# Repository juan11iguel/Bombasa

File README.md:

# Bombasa
En este proyecto intentamos implementar un arduino, con un driver para un motor DC y, haciendo uso de periféricos como una pantalla de 4 dígitos y 7 segmentos, así como de botones, interruptores, etc. Establecer dos modos de funcionamiento en un sistema cuyo objetivo es el impulso de reactivos químicos para mezcla de componentes (bomba PERISTÁLTICA*):

- El modo manual tiene como entrada la pulsación de dos botones, uno para aumentar y otro para disminuir, el rango de valores va de 0 a 20, y cada valor se corresponde con un valor de voltaje que se le introduce al motor y que hace propulsar un caudal determinado tras la calibración. El valor escogido, así como el voltaje que le corresponde y su caudal se muestran periódicamente en pantalla, así como en una tabla situada en la parte superior de la caja.
- El modo automático tiene dos opciones de funcionamiento, o bien toma la información de una tarjeta de entrada/salida (Labjack), que proporciona valores comprendidos entre 0 y 5V, el valor es leído por el Arduino en uno de sus puertos analógicos y codificado entre 0 y 1023, lo que a su vez ajusta al valor del PWM (0 - 255) y se introduce al driver. Otra opción es hacer uso de la comunicación por el puerto serie, que admite desde valores de la terminal serie incluída en el entorno de desarrollo de arduino, o bien a través de programas como Matlab (pendiente) o un sencillo programa desarrollado en Python (ya hecho y funcionando). 

Posteriormente, se intentará introducir un caudalímetro contador, que se introducirá en uno de los puertos digitales del Arduino, y se desarrollará un algoritmo para acondicionar esa información entrante y convertirla en un valor de caudal que se actualice cada pocos segundos, esta información se usará para cerrar un lazo de control, y haciendo uso de un controlador tipo PI controlar la bomba. También la idea es mandar la información instantánea del caudal como salida para poder realizar el registro de la información tomada.

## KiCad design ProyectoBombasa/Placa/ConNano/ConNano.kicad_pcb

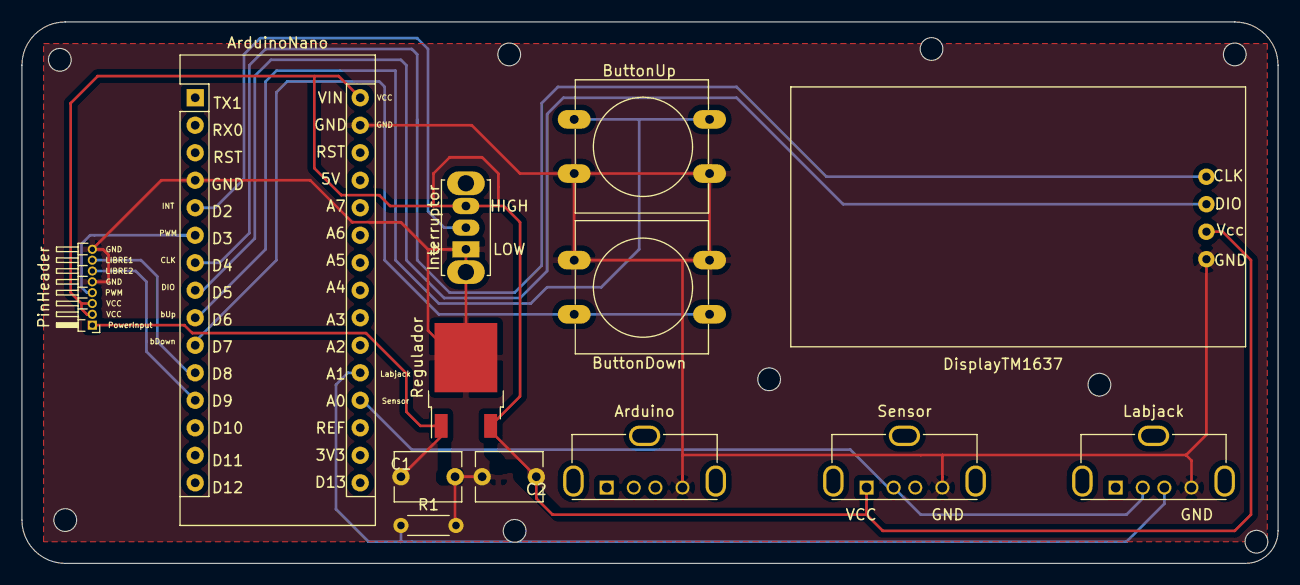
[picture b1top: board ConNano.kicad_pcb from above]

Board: 2 copper layers, 116.0 x 50.0 mm, 13 parts (0 on the bottom side), 13 nets.

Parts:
Arduino: USB_A; USB_A_Molex_105057_Vertical
ArduinoNano: Arduino_Nano_v3.x; Arduino_Nano
ButtonDown: SW_Push; SW_PUSH-12mm
ButtonUp: SW_Push; SW_PUSH-12mm
C1: 0.33uF; C_Disc_D6.0mm_W4.4mm_P5.00mm
C2: 0.1uF; C_Disc_D6.0mm_W4.4mm_P5.00mm
DisplayTM1637: TM1637; TM1637Cool
Interruptor: SW_SPDT; SW_Slide_1P2T_CK_OS102011MS2Q
Labjack: USB_A; USB_A_Molex_105057_Vertical
PinHeader: Conn_01x08; PinHeader_1x08_P1.00mm_Horizontal
R1: 1k; R_Axial_DIN0204_L3.6mm_D1.6mm_P5.08mm_Horizontal
Regulador: L7805; TO-252-2
Sensor: USB_A; USB_A_Molex_105057_Vertical

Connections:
ButtonDown: ArduinoNano.10, ButtonDown.2
ButtonUp: ArduinoNano.9, ButtonUp.1
CLK: ArduinoNano.7, DisplayTM1637.1
DIO: ArduinoNano.8, DisplayTM1637.2
GND: Arduino.4, ArduinoNano.4, ButtonDown.1, ButtonUp.2, C1.2, C2.2, DisplayTM1637.4, Interruptor.1, Labjack.4, PinHeader.5, PinHeader.8, R1.2, Regulador.2, Sensor.4
Interruptor: ArduinoNano.5, Interruptor.2
LabjackSC: ArduinoNano.20, Labjack.3, R1.1
LabjackSensor: ArduinoNano.19, Labjack.2, Sensor.2
PWM: ArduinoNano.6, PinHeader.4
PowerInput: C1.1, PinHeader.1, Regulador.1
Vcc: ArduinoNano.30, C2.1, DisplayTM1637.3, Interruptor.3, PinHeader.2, PinHeader.3, Regulador.3, Sensor.1
porSiAca1: ArduinoNano.11, PinHeader.6
porSiAca2: ArduinoNano.12, PinHeader.7

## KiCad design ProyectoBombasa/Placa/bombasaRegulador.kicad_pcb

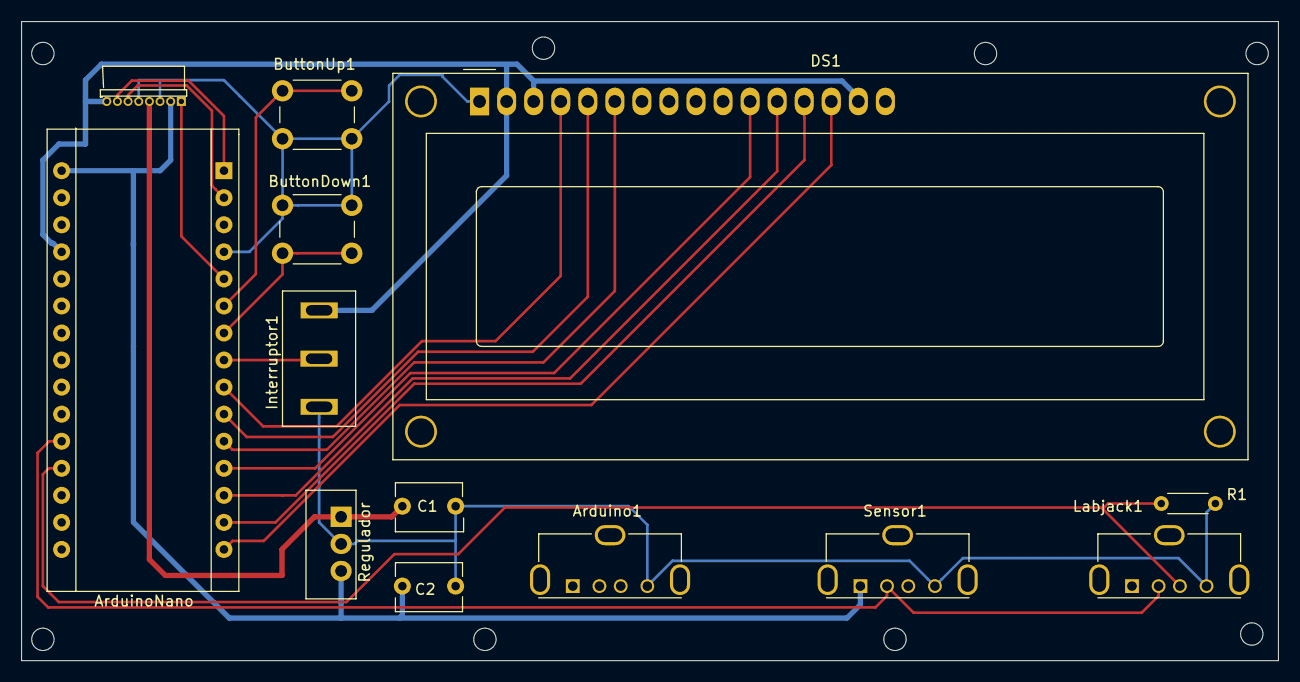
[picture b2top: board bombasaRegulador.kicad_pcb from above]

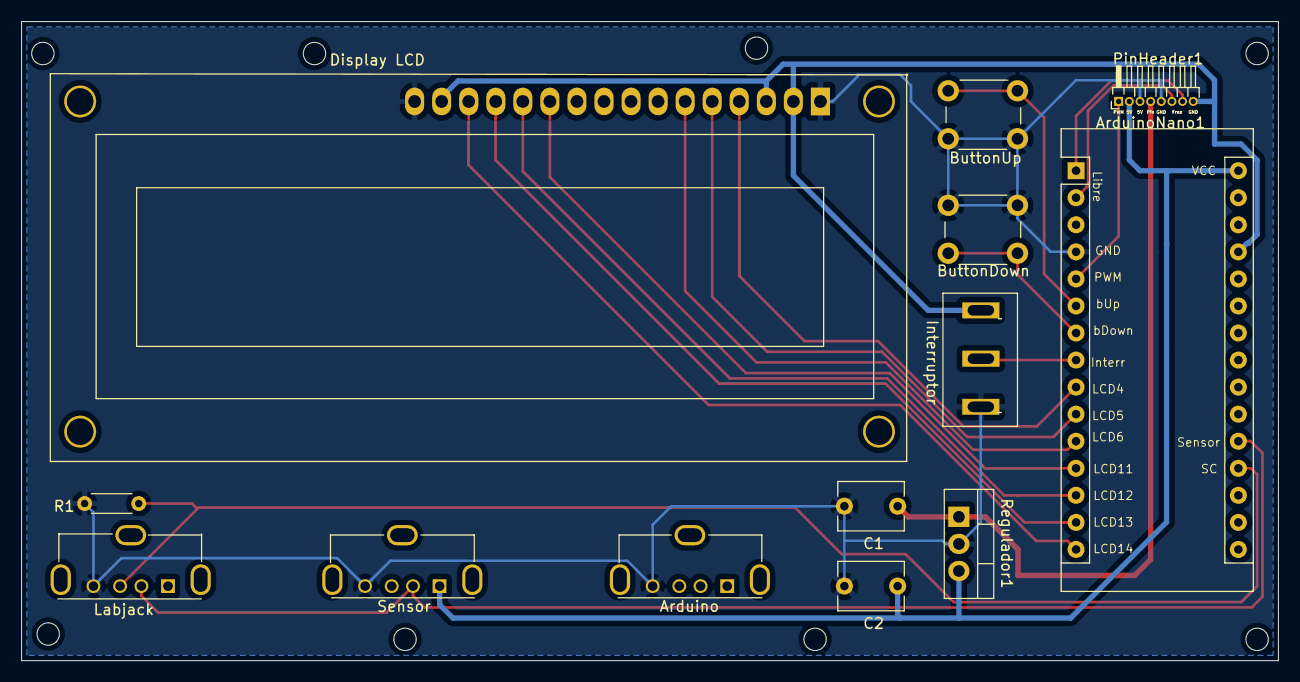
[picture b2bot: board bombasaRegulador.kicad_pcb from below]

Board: 2 copper layers, 118.0 x 60.0 mm, 13 parts (6 on the bottom side), 19 nets.

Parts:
Arduino1: USB_A; USB_A_Molex_105057_Vertical
ArduinoNano1: Arduino_Nano_v3.x; Arduino_Nano
ButtonDown1: SW_Push; SW_PUSH_6mm_H13mm
ButtonUp1: SW_Push; SW_PUSH_6mm_H13mm
C1: 0.33uF; C_Disc_D6.0mm_W4.4mm_P5.00mm
C2: 0.1uF; C_Disc_D6.0mm_W4.4mm_P5.00mm
DS1: WC1602A
Interruptor1: SW_SPDT; Interruptor
Labjack1: USB_A; USB_A_Molex_105057_Vertical
PinHeader1: Conn_01x08; PinHeader_1x08_P1.00mm_Horizontal
R1: 1k; R_Axial_DIN0204_L3.6mm_D1.6mm_P5.08mm_Horizontal
Regulador1: L7812; TO-220-3_Vertical
Sensor1: USB_A; USB_A_Molex_105057_Vertical

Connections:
5V: ArduinoNano1.27, DS1.2, DS1.3, DS1.15, Interruptor1.3, PinHeader1.5V
ButtonDown: ArduinoNano1.7, ButtonDown1.2
ButtonUp: ArduinoNano1.6, ButtonUp1.1
GND: Arduino1.4, ArduinoNano1.4, ButtonDown1.1, ButtonUp1.2, C1.2, C2.2, DS1.1, DS1.16, Interruptor1.1, Labjack1.4, PinHeader1.3, PinHeader1.5, R1.2, Regulador1.2, Sensor1.4
Interruptor: ArduinoNano1.8, Interruptor1.2
LCD4: ArduinoNano1.9, DS1.4
LCD5: ArduinoNano1.10, DS1.5
LCD6: ArduinoNano1.11, DS1.6
LCD11: ArduinoNano1.12, DS1.11
LCD12: ArduinoNano1.13, DS1.12
LCD13: ArduinoNano1.14, DS1.13
LCD14: ArduinoNano1.15, DS1.14
LabjackSC: ArduinoNano1.19, Labjack1.3, R1.1
LabjackSensor: ArduinoNano1.20, Labjack1.2, Sensor1.2
PWM: ArduinoNano1.5, PinHeader1.1
PowerInput: C1.1, PinHeader1.4, Regulador1.1
Vcc: ArduinoNano1.30, C2.1, PinHeader1.2, Regulador1.3, Sensor1.1
porSiAca1: ArduinoNano1.2, PinHeader1.6
porSiAca2: ArduinoNano1.1, PinHeader1.7

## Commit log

2019-03-18 Add files via upload
    Librerías necesarias para poder compilar y subir el programa Bombasa.ino
2019-03-18 Carpeta contenedora del proyecto
2019-03-19 Última actualisasió
    Añade la característica de que muestre en pantalla MAN o AUTO cuando se conmuta de modo.
2019-03-19 Versión Base sobre la que trabajar
2019-03-19 Arreglado problema display
    Ahora ya muestra correctamente todos los decimales, he añadido round() a cuando sacaba la parte decimal como entera.
2019-03-20 Ultima version
    Actualizado el sketch caudalimetro para intentar implementar leer la frecuencia con el contador, pero principalmente para intentar leer el voltaje que se le introduce al motor.
2019-03-22 Para probar a representar la medida en tiempo real
2019-03-22 Código Matlab
    Código Matlab para representación y tratamiento de datos.
2019-03-23 Inclusión librería pantalla y PID
2019-03-23 Última versión de Caudalimetro
    Añadidos algunos comentarios y limpiado un poco el código.
    Tareas pendientes:
    - Hacer subprograma caudalimetro que devuelva el caudal cada x tiempo como la media de los valores tomados en ese intervalo.
    - Añadir a leerVoltaje para que devuelva cada x tiempo la media de los valores leídos en ese intervalo.
    - Incluir el controlador para el control automático del voltaje enviado para seguir la consigna de entrada.
    - Sacar modelos para diseñar controladores.
2019-03-24 Cambio de algunos nombres para organizar mejor.
2019-03-24 Función LecturaVoltaje()
    Actualizada la función LecturaVoltaje para que almacene cien valores, y presente en pantalla la media de esos cien valores cada 1 seg, así se consigue una lectura más limpia. Vmedio sería el valor ob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
2019-03-24 Actualización nombre
    Bombasa -> Bombasa_BA (Bombasa Bucle abierto)
2019-03-24 Añadido leerCaudal()
    Añadido la función de leer caudal, en el estado actual devuelve un valor de frecuencia como el valor medio de 100 valores, similar al voltaje.
2019-03-24 Eliminados Sketchs antiguos
    El de la pantalla ya no es necesario porque está integrado en los de Bombasa y el de comunicación igual, ejecutando cualquiera de los dos se pueden probar y ya se han probado que funcionan correctame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
2019-03-24 Inclusión Base para el PID
    De momento todo comentado, pero incluído lo que teóricamente se necesita para el PID a falta de determinar planta y parámetros, además de intentar incluir la modificación para lo de la zona muerta.
    Este es el archivo para el BC, falta ver cómo meter que en manual sólo modifique las referencias, y en automático lo mismo, pero al final todos llamen al controlador.
    El de Bucle abierto habría que actualizarlo pues faltan varias cosas importantes, copiando el bucle cerrado antes de dejarlo hecho y quitando toda la parte del controlador.
2019-03-24 Actualizado con sensores
    Última versión con los subprogramas de los sensores. Falta añadir la funcionalidad de que vaya conmutando la pantalla entre mostrar el valor real de voltaje enviado al motor y el caudal propulsado.
    En manual: Que mantenga durante unos dos segundos la opción escogida (0-20), y que luego inicie a oscilar entre Voltaje y caudal.
    En automático, que muestre unos segundos el valor introducido (de 0 a 100) y después oscile.
2019-03-24 Base PID + actualizado MANUAL y AUTO
    Incluído lo que teóricamente se necesita para el PID a falta de determinar planta y parámetros, además de intentar incluir la modificación para lo de la zona muerta.
    Nuevo: Ahora el modo manual sólo sirve para cambiar la referencia si se está en Bucle Cerrado.
    Igual para el modo automático, lee valores de voltaje deseado (0-100) y los introduce como referencia al PID.
2019-03-29 Última versió
2019-03-30 Añadido el PID con control adaptativo
2019-03-31 Registra la lectura del sensor en un archivo
2019-03-31 Registra la lectura del sensor en un archivo te t
2019-03-31 Era un archivo temporal
2019-03-31 Limpieza
2019-04-01 Implementado en el sistema real funcionando correctamente
2019-04-02 Add files via upload
    Simulación del Breadboard en Fritzing
2019-04-02 Jesís
2019-04-02 LogToFile
2019-04-04 Debugginn bersion
2019-04-07 Última versión
    Incluye el programa para mostrar la gráfica en tiempo real
2019-04-23 Añadido PCB
